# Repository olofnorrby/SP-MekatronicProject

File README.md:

# SP-MekatronicProject
A school project about creating a Regulator

s=tf('s');
h=0.8
GR=2.282*(1+(1/(55.55*s)))
H=c2d(GR,h,'tustin')
format long
H.den{1}
H.num{1}
%2.2984320
%-2.2655679

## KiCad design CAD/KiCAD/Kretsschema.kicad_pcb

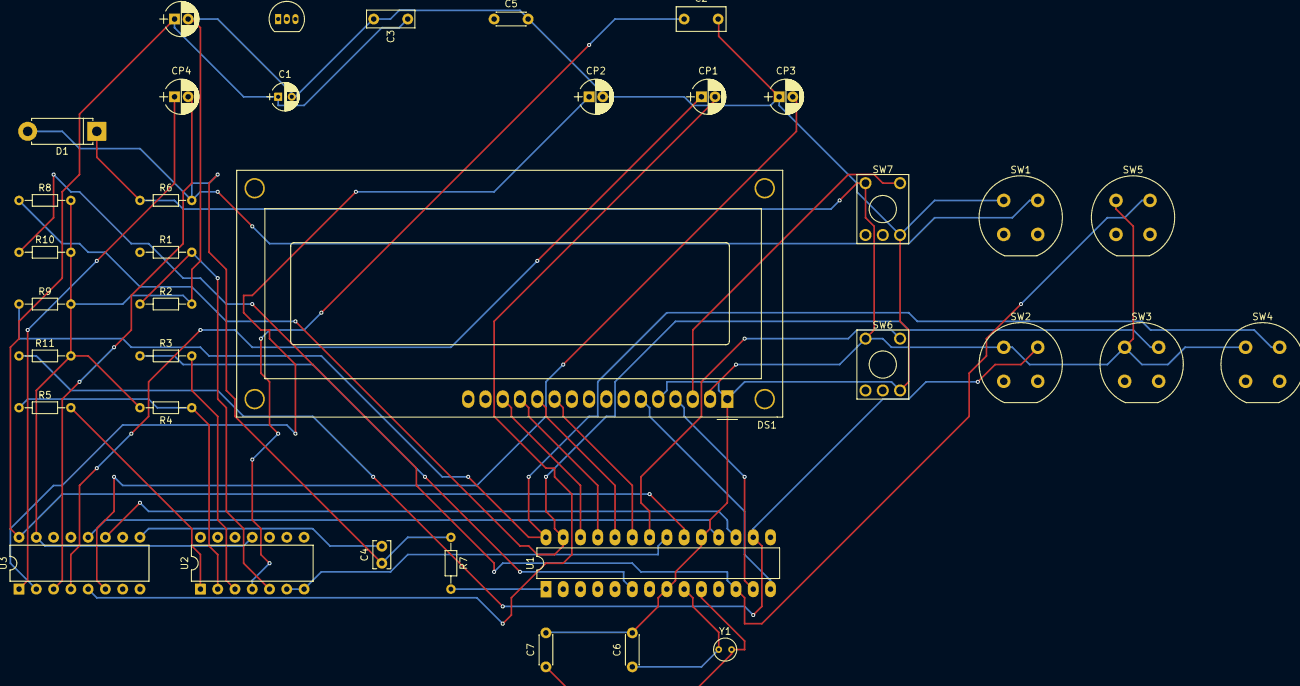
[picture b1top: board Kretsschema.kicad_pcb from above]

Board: 2 copper layers, 37 parts (0 on the bottom side), 35 nets.

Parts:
C1: 1µF; CP_Radial_D4.0mm_P2.00mm
C2: 0.33µF; C_Rect_L7.2mm_W3.5mm_P5.00mm_FKS2_FKP2_MKS2_MKP2
C3: 0.1µF; C_Rect_L7.0mm_W2.5mm_P5.00mm
C4: 0.1µF; C_Rect_L4.0mm_W2.5mm_P2.50mm
C5: 4.7µF; C_Disc_D4.3mm_W1.9mm_P5.00mm
C6, C7: 15pF; C_Disc_D4.3mm_W1.9mm_P5.00mm
CP1, CP2, CP3, CP4, CP5: 1µF; CP_Radial_D5.0mm_P2.00mm
D1: 1N4148; D_5W_P10.16mm_Horizontal
DS1: BC1602A; WC1602A
R1, R2: 320kΩ; R_Axial_DIN0204_L3.6mm_D1.6mm_P7.62mm_Horizontal
R3: 1.5kΩ; R_Axial_DIN0204_L3.6mm_D1.6mm_P7.62mm_Horizontal
R4, R5: 10kΩ; R_Axial_DIN0204_L3.6mm_D1.6mm_P7.62mm_Horizontal
R6: 33kΩ; R_Axial_DIN0204_L3.6mm_D1.6mm_P7.62mm_Horizontal
R7, R8, R9, R10, R11: 1kΩ; R_Axial_DIN0204_L3.6mm_D1.6mm_P7.62mm_Horizontal
SW1: MCLR; Push_E-Switch_KS01Q01
SW2: Timmar; Push_E-Switch_KS01Q01
SW3: Minuter; Push_E-Switch_KS01Q01
SW4: Sekunder; Push_E-Switch_KS01Q01
SW5: Rampfunktion; Push_E-Switch_KS01Q01
SW6: Set Value; KSA_Tactile_SPST
SW7: LCD Contrast; KSA_Tactile_SPST
U1: PIC18F25K22; DIP-28_W7.62mm_LongPads
U2: LM324N; DIP-14_W7.62mm
U3: MAX232; DIP-16_W7.62mm
U4: 78L05; TO-92_Inline_Narrow_Oval
Y1: 4MHz; Crystal_C38-LF_d3.0mm_l8.0mm_Vertical

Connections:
+5V: D1.1, DS1.2, R6.1, SW2.1, SW3.1, SW4.1, SW5.1, SW6.1, SW7.1
+15V: C2.1, U2.4
GND: C1.2, C2.2, C3.2, C5.2, C6.2, C7.2, CP2.2, CP3.1, CP5.2, DS1.1, DS1.5, R2.2, R4.2, R8.2, R9.2, R10.2, R11.2, SW1.1, SW6.3, SW7.3, U1.8, U1.19, U2.11, U3.15
unnamed: C1.1, C3.1, CP5.1, U1.20, U3.16
unnamed: C4.1, D1.2, R6.2, R7.1, SW1.2
unnamed: C4.2, U3.9
unnamed: C6.1, U1.9, Y1.1
unnamed: C7.1, U1.10, Y1.2
unnamed: CP1.1, U3.4
unnamed: CP1.2, U3.5
unnamed: CP2.1, U3.2
unnamed: CP3.2, U3.6
unnamed: CP4.1, U3.1
unnamed: CP4.2, U3.3
unnamed: DS1.3, SW7.2
unnamed: DS1.4, U1.13
unnamed: DS1.6, U1.14
unnamed: DS1.11, U1.23
unnamed: DS1.12, U1.24
unnamed: DS1.13, U1.25
unnamed: DS1.14, U1.26
unnamed: R1.2, R2.1, U2.5
unnamed: R3.1, U1.6
unnamed: R3.2, U2.3
unnamed: R4.1, R5.1, U2.2
unnamed: R7.2, U1.1
unnamed: R8.1, SW3.2, U1.27
unnamed: R9.1, SW4.2, U1.28
unnamed: R10.1, SW5.2, U1.12
unnamed: R11.1, SW2.2, U1.16
unnamed: SW6.2, U1.22
unnamed: U1.17, U3.11
unnamed: U1.18, U3.12
unnamed: U1.21, U2.6, U2.7
Styrsignal,0-10V: R5.2, U2.1

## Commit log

2017-08-31 Create Arbetslogg
2017-08-31 Update Arbetslogg
2017-09-07 Create Data Sheets
2017-09-07 test
2017-09-08 pass3
2017-10-11 update on rapport
2017-10-12 Create KiCad_files
2017-10-13 Final update
    The final update of the pic code, tested and aproved!
2017-10-13 Added Untitled Diagram.xml
2017-10-13 Added Untitled Diagram.jpg
2017-10-15 Added Flowchart1.xml
2017-10-15 Added Flodesschema.xml
2017-10-15 Added Flodesschema.jpg
2017-10-15 Added OP2.xml
2017-10-15 Added OP2.jpg
2017-10-15 Added lowpassfilter.jpg
2017-10-15 Added OP1.xml
2017-10-15 Added OP2.png
